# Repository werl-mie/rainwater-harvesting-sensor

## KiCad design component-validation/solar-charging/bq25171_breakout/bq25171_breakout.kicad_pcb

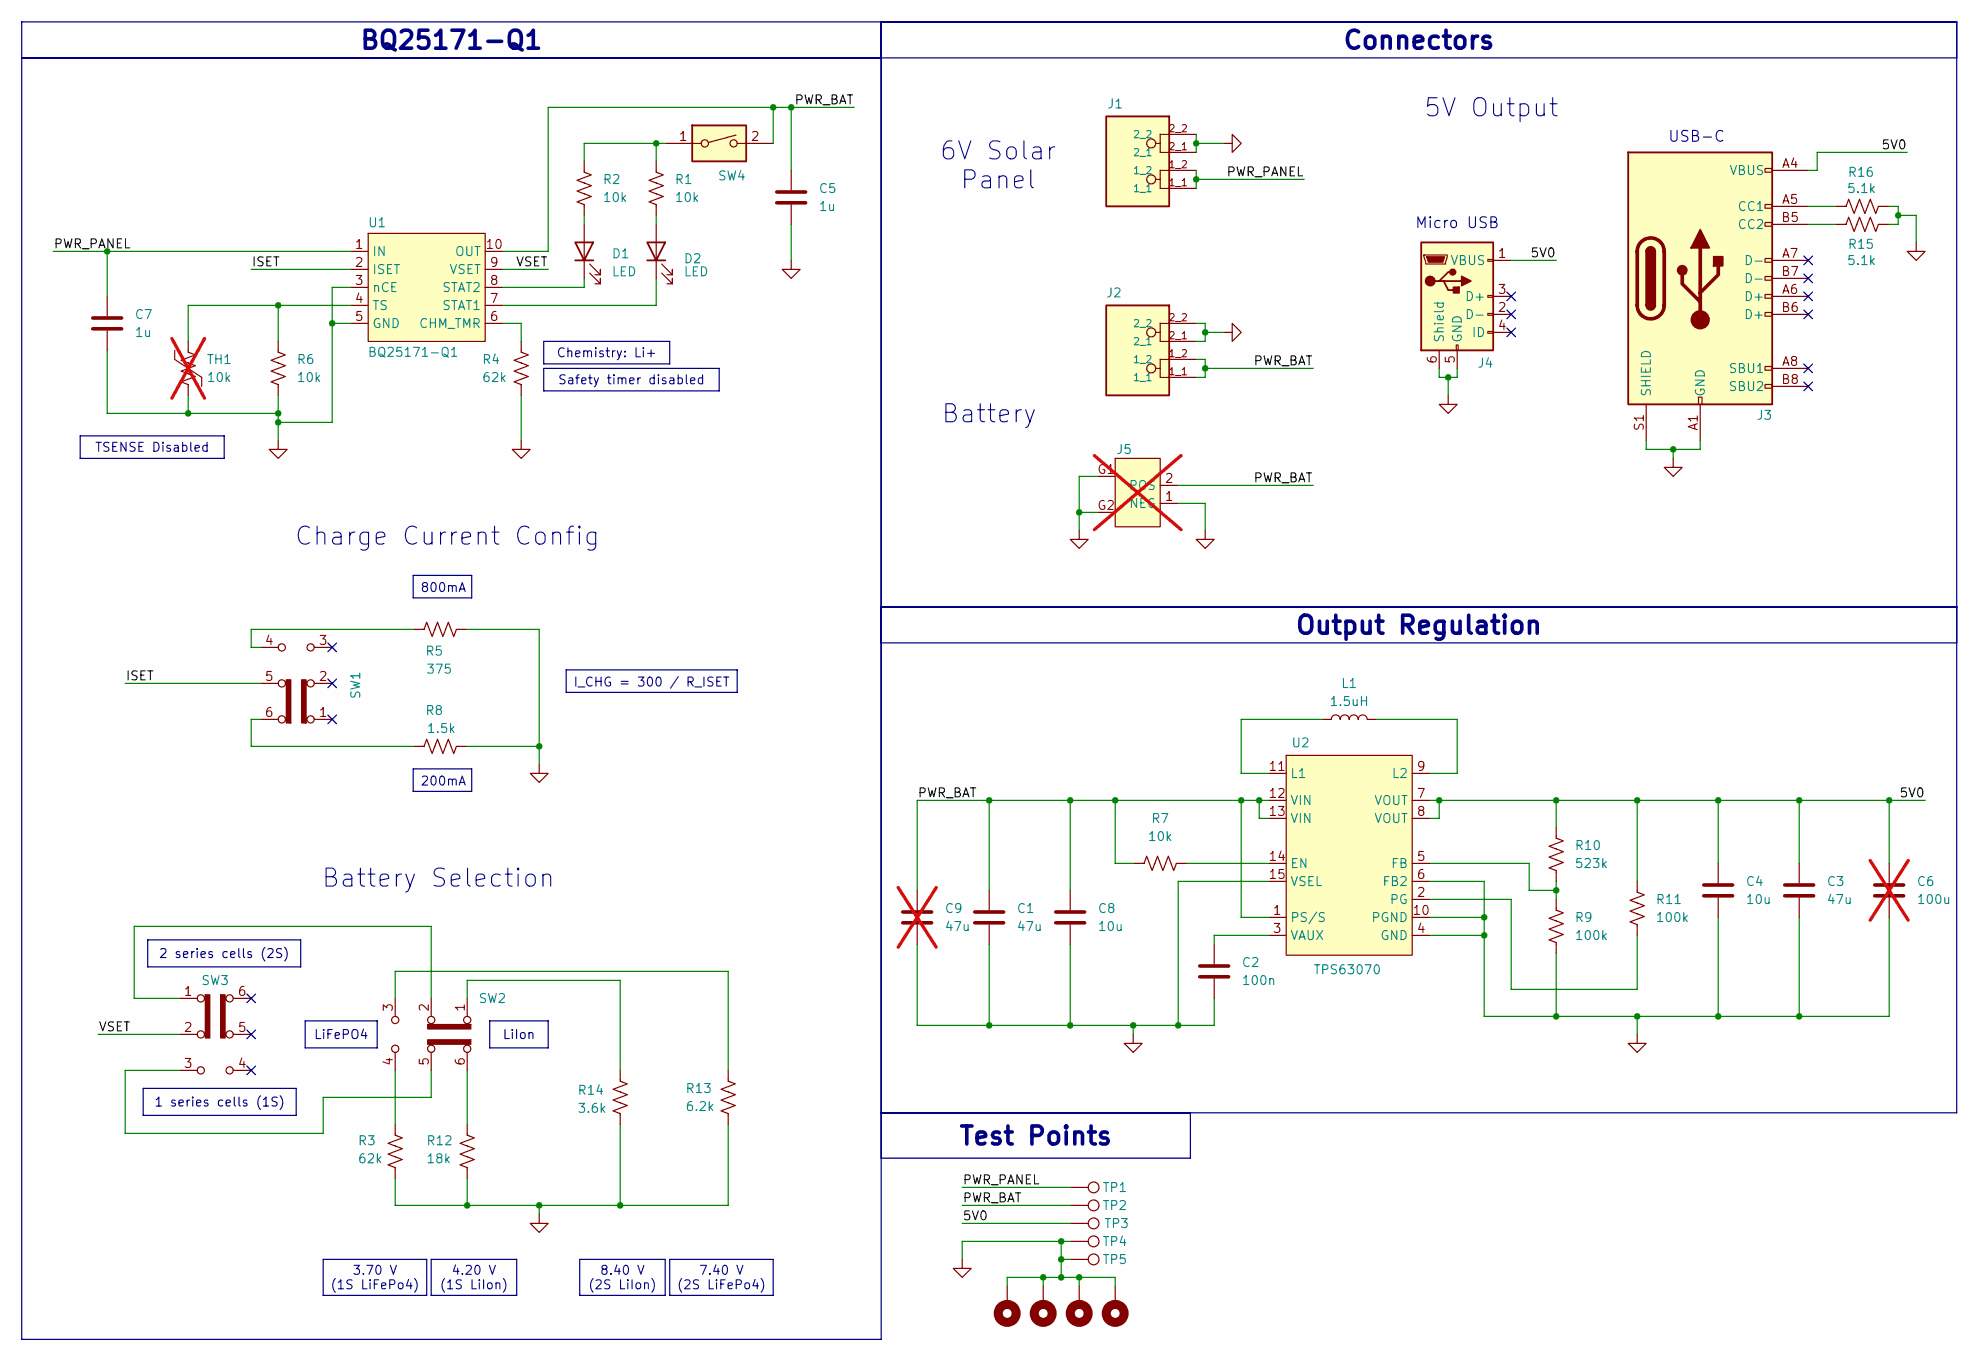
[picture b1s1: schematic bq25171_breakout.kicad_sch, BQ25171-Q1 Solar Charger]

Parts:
C1, C3: 47u; C_1210_3225Metric_Pad1.33x2.70mm_HandSolder
C2: 100n; C_0603_1608Metric_Pad1.08x0.95mm_HandSolder
C4, C8: 10u; C_0603_1608Metric_Pad1.08x0.95mm_HandSolder
C5, C7: 1u; C_0603_1608Metric_Pad1.08x0.95mm_HandSolder
C6: 100u; C_0805_2012Metric_Pad1.18x1.45mm_HandSolder; not fitted
C9: 47u; C_0805_2012Metric_Pad1.18x1.45mm_HandSolder; not fitted
D1, D2: LED; LED_0603_1608Metric
H1, H2, H3, H4: MountingHole_Pad; MountingHole_3.2mm_M3_ISO14580_Pad
J1, J2: 1017503; PHOENIX_1017503; PARTREV 22.12.2017
J3: USB_C_Receptacle_USB2.0_16P; USB_C_Receptacle_XKB_U262-16XN-4BVC11; MPN 12401610E4
J4: USB_B_Micro; USB_Micro-B_Amphenol_10118193-0002LF_Horizontal; MPN 10118193-0002LF
J5: JST_PH_S2B-PH-SM4-TB_1x02-1MP_P2.00mm_Horizontal; not fitted
L1: 1.5uH; L_Changjiang_FXL0420; MPN FXL0420-1R5-M
R1, R2, R6, R7: 10k; R_0603_1608Metric_Pad0.98x0.95mm_HandSolder
R3: 62k; R_0603_1608Metric_Pad0.98x0.95mm_HandSolder; Tolerance 1%
R4: 62k; R_0603_1608Metric_Pad0.98x0.95mm_HandSolder
R5: 375; R_0603_1608Metric_Pad0.98x0.95mm_HandSolder
R8: 1.5k; R_0603_1608Metric_Pad0.98x0.95mm_HandSolder
R9, R11: 100k; R_0603_1608Metric_Pad0.98x0.95mm_HandSolder
R10: 523k; R_0603_1608Metric_Pad0.98x0.95mm_HandSolder
R12: 18k; R_0603_1608Metric_Pad0.98x0.95mm_HandSolder; Tolerance 1%
R13: 6.2k; R_0603_1608Metric_Pad0.98x0.95mm_HandSolder; Tolerance 1%
R14: 3.6k; R_0603_1608Metric_Pad0.98x0.95mm_HandSolder; Tolerance 1%
R15, R16: 5.1k; R_0603_1608Metric_Pad0.98x0.95mm_HandSolder
SW1, SW2, SW3: SW_Slide_DPDT; JLC_SHOU-HAN_MST22D18G2; MPN MST22D18G2
SW4: SW_DIP_x01; JLC_DongGuan_DSIC01LSGET
TH1: 10k; R_Axial_DIN0204_L3.6mm_D1.6mm_P2.54mm_Vertical; MPN 103AT-4; not fitted
TP1, TP2, TP3: TestPoint; TestPoint_Keystone_5000-5004_Miniature
TP4, TP5: TestPoint; TestPoint_Keystone_5019_Miniature
U1: BQ25171-Q1; TI_VSON10_BQ25171; MPN BQ25171-Q1
U2: TPS63070; TI_VQFN15_TPS63070RNMR

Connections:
/5V0: C3.2, C4.2, C6.2, J3.A4 (VBUS), J3.A9 (VBUS), J3.B4 (VBUS), J3.B9 (VBUS), J4.1 (VBUS), R10.1, R11.2, TP3.1, U2.7 (VOUT), U2.8 (VOUT)
/ISET: SW1.5 (B), U1.2 (ISET)
/PWR_BAT: C1.2, C5.2, C8.1, C9.2, J2.1_1, J2.1_2, J5.2 (POS), R7.2, SW4.2, TP2.1, U1.10 (OUT), U2.1 (PS/S), U2.12 (VIN), U2.13 (VIN)
/PWR_PANEL: C7.2, J1.1_1, J1.1_2, TP1.1, U1.1 (IN)
/VSET: SW3.2 (B), U1.9 (VSET)
GND: C1.1, C2.1, C3.1, C4.1, C5.1, C6.1, C7.1, C8.2, C9.1, H1.1, H2.1, H3.1, H4.1, J1.2_1, J1.2_2, J2.2_1, J2.2_2, J3.A1 (GND), J3.A12 (GND), J3.B1 (GND), J3.B12 (GND), J3.S1 (SHIELD), J4.5 (GND), J4.6 (Shield), J5.1 (NEG), J5.G1, J5.G2, R3.1, R4.1, R5.1, R6.1, R8.1, R9.2, R12.1, R13.1, R14.1, R15.2, R16.2, TH1.2, TP4.1, TP5.1, U1.3 (nCE), U1.5 (GND), U1.GND, U2.4 (GND), U2.6 (FB2), U2.10 (PGND), U2.15 (VSEL)
unnamed: D1.2 (A), R2.1
unnamed: D1.1 (K), U1.8 (STAT2)
unnamed: D2.2 (A), R1.1
unnamed: D2.1 (K), U1.7 (STAT1)
unnamed: J3.A5 (CC1), R16.1
unnamed: J3.B5 (CC2), R15.1
unnamed: R1.2, R2.2, SW4.1
unnamed: R3.2, SW2.4 (A)
unnamed: R5.2, SW1.4 (A)
unnamed: R8.2, SW1.6 (C)
unnamed: R12.2, SW2.6 (C)
unnamed: R13.2, SW2.3 (C)
unnamed: R14.2, SW2.1 (A)
unnamed: SW2.2 (B), SW3.1 (A)
unnamed: SW2.5 (B), SW3.3 (C)
unnamed: R4.2, U1.6 (CHM_TMR)
unnamed: R6.2, TH1.1, U1.4 (TS)
unnamed: R7.1, U2.14 (EN)
unnamed: R9.1, R10.2, U2.5 (FB)
unnamed: L1.1, U2.11 (L1)
unnamed: L1.2, U2.9 (L2)
unnamed: R11.1, U2.2 (PG)
unnamed: C2.2, U2.3 (VAUX)

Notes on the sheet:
Micro USB
USB-C
Battery
Charge Current Config
5V Output
Battery Selection
6V Solar Panel
4.20 V (1S LiIon)
LiFePO4
BQ25171-Q1
200mA
7.40 V (2S LiFePo4)
8.40 V (2S LiIon)
TSENSE Disabled
Chemistry: Li+
I_CHG = 300 / R_ISET
1 series cells (1S)
800mA
2 series cells (2S)
Test Points
LiIon
Connectors
3.70 V (1S LiFePo4)
Safety timer disabled
Output Regulation

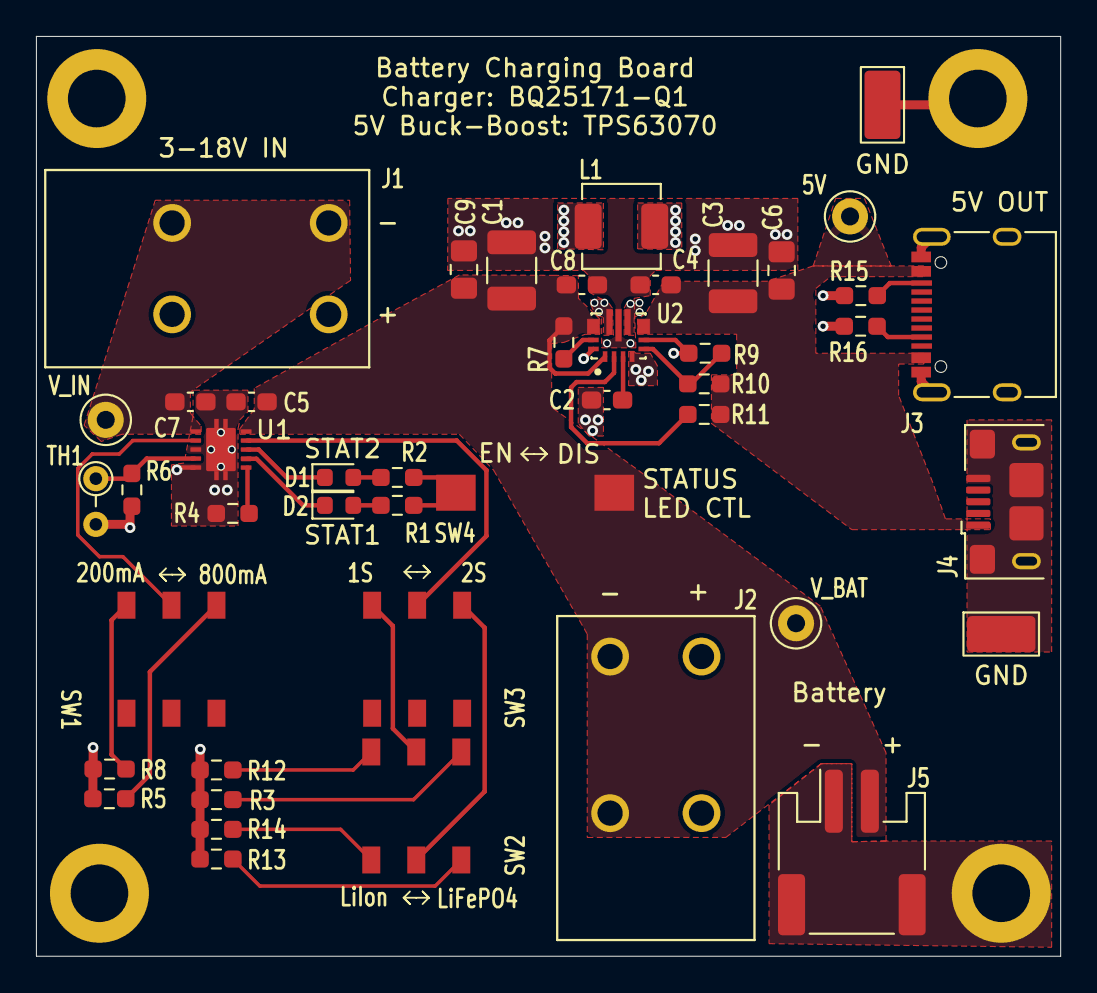
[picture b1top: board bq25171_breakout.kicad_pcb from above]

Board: 2 copper layers, 56.9 x 51.1 mm, 49 parts (0 on the bottom side), 29 nets.

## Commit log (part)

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2023-07-16 Added MWEs for basic FW functionality
2023-07-17 Basic float sensor logging
    Implemented the following functionality:
    - Takes float sensor change as an interrupt (either while sleeping or awake), flagging the change and saving the value into a buffer variable
    - Main loop checks for the flag, which triggers a write to SD card
2023-07-18 Completed code for MWE_InternalRTCBlink
    Used an alarm generated with the internal RTC to blink an LED. Have to set the alarm time to the target time less 1 second, because for some reason when the current time is retrieved with the API, th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
    Verified that the code works when seconds overflows.
2023-07-18 Created MWE_EventTimeoutWithInternalRTC.ino
2023-07-19 Implemented continuous logging timeout
    Notes:
    - Realized I would need to save time of first trigger in order to figure out an interval at the end of the measurement period
    - Due to misunderstanding of the bucket operation, had to change interrupt trigger to FALLING (magnet only activates reed switch in the middle of tipping, NOT at either end)
    - Needed to add a capacitor to debounce the tip bucket reed switch
2023-07-19 Remove attachInterrupts
    Tested this and it turns out they are redundant
2023-07-19 Atomized log_to_sd()
    Made the functionality less specific so that it can used more flexibly (print with/without linebreak, with/without timestamp)
2023-07-20 Added code for 2 extra float sensors
2023-07-21 Removed Serial prints for running off battery
2023-07-24 Fixed debug LED blinking
    debug LEDs that I implemented were not blinking because I have the delay() in code sections without interrupts. Moved the error blinks out of sections where interrupts are disabled...
2023-07-24 Leak test
    Constantly logging periodic data to see if when it stops working. Seems that memory runs out after around 16 seconds (134 logs)
2023-07-24 Removed remaining variable initializations in loops/ISRs
    Also includes:
    - BUILTIN_LED blink as health check
2023-07-24 Removed AHT code
2023-07-24 Added battery voltage monitoring
2023-07-27 Adjusting constants, added log file
2023-07-27 Added watchdog
2023-08-01 Added log files from second test
2023-08-01 Added basic functinoality
    Using D0 and D1 pins. Should test functionality sharing D13 with LED_BUILTIN.
2023-08-18 Code flashed for field trial 1
    - configured pins
    - set bucket timeout to 10
    - added AM2320 code to PCF8523 code
    - added logging of health check
    - removed serial print
2023-10-06 initialized docsify
    includes mermaid test
2023-10-06 removed mermaid test
2023-10-06 Trigger rebuild
2023-10-06 test - removed docsify files
2023-10-06 re-added index.html, removed .nojekyl
2023-10-06 manual index.html test
2023-10-06 Trying building from root
2023-10-06 re-trying build from docs
2023-10-06 Renaming readme.md -> README.md
2023-10-06 removed docs files from root
2023-10-18 initial data cleanup and plotting functionality
    - Reformatting (input -> pre-process2.py -> out.csv)
    - Basic data clean (out.csv -> data_cleanup.py -> out_clean.csv)
    - Basic timescale plotting (plot_time_mpl.py)
2023-10-24 Improved filtering of bucket data and integrated rainfall weather data
2023-10-29 Final fix to extraneous bucket count filtering
2023-11-03 Added cad for V1 sensor
2023-11-24 Added documentation and bucket count conversion
2023-11-24 Attempt to modify example code to work on UNO
2023-11-28 Added bucket-count conversion and resampling
2023-11-30 modified code to work on feather
2023-12-19 Consolidate level data into tank data
    To simplify communication of graphs to Martin
2024-01-08 renamed v1 code folder
2024-01-23 Combined tank level processing with bucket count to rainfall conversion
2024-01-23 Renamed and reorganized folder
2024-01-23 more name changes
2024-01-24 Added script to convert csv to influxDB line format
2024-02-12 Misc progress
    - read-current script for arduino
    - script to parse and publish arduino serial data (influx-publish.py)
    - re-organizing lora code
2024-02-12 Create mwe_grove_tx-rx
    Basic example of tx/rx w/o handshake
2024-02-22 Changes to parsability
    - Added 'tx' and 'rx' headers to serial messages sent from tx/rx nodes to RPi
    - Replaced COTTON_CANDY_ID in read-current.ino with 'cc' header
2024-02-25 Incorrect implementation of check_packets
    function to check for missed vs. received packets. This version won't work as-is because the deque() is being modified as I iterate through it.
2024-02-28 Implemented packet loss checking
    - Basic implementation of linked list to support this
    - Wrote simple test with test data
2024-02-29 Code to run first basic experiment without influx publishing
2024-03-11 lora rx improvements (+ minor power-experiment fix)
    mwe_grove_tx-rx.ino
    - 'fixed' bug where every other tx packet was dropped
    lora-experiment2.py
    - fixed issue where only 1 rx was being read for each 3 tx
    - online missed packet tracking is NOT WORKING
    influx-pubilsh2.py
2024-04-08 Sleeping LoRa module
2024-04-10 v2-cad
2024-04-10 new pot cover assembly
    pot-holder.sldasm
2024-04-11 pot-coupling-v6 changes
    - Made potentiometer slot larger (4.6 -> 4.8 mm)
    - Lowered depth of set screw boss
2024-04-15 pot assembly updates
    pot-coupling-v8
    - Using experimentally validated thread profile diameter (19.8mm)
    pot-holder-3
    - changed angle
2024-04-16 misc changes
    - 5mm slotted hole test
    - enclosure cutout
    - 20mm threaded hole test
2024-04-18 bracket
2024-05-06 Added cellular functionality example code
2024-05-09 Working example of parsing strings from Gateway
2024-05-13 Added main.ino for Arduino MKR NB 1500
    Basic functionality to publish json data
2024-05-13 Update main.ino
    - Added watchdog surrounding only mqqtConnect.
    - Added macro to enable/disable all Serial output
2024-05-14 Cellular - added watchdog
    Keeping the watchdog disabled during cellular (re)connection
2024-05-14 Fixed incorrect parsing of node/parent addresses
2024-05-15 Basic working Tx/Rx
    Tx code: Removed timeout from node_recv()
    Rx code: Removed node_send() (although battery consumption isn't a huge concern anyways)
2024-05-19 wifi changes
    star_rx: adding parsing by message ID
    star_tx: configuring pins
    wifi:
    - adding serial monitor python script for modification
    - Adding wpa_supplicant template
2024-05-20 Basic working serial monitor + tx_rx lora code
2024-05-20 Added tx sd logging
2024-05-20 rx sd card logging
2024-05-20 Flashed Rx/Tx code
    Label "Version 1.0"
2024-07-23 misc reorganizations?
2024-10-26 Parsing of RPi data from sylvias
    Also began data analysis notebook
2025-04-08 misc stuff
2025-04-28 Added solar charging board
2025-06-29 Added sample_grove_rx_and_wire code
2025-07-04 Adriana's LoRa
2025-09-18 Serial output tipping bucket counter
2025-09-18 Create Component_Serial_Tests
2025-09-18 Create rainBucket
2025-10-04 Added nrf_cloud sample
2025-10-11 Remove build files in gitignore
2025-10-12 Created readme and organized files by device
2026-02-20 Create v4_CZ folder
2026-02-20 Create v4_CZ folder attempt 2
2026-02-20 Create RX_ino
2026-02-20 success only sending A0 sensor data
    RADIO_RAW: +TEST: LEN:10, RSSI:-56, SNR:13
    RADIO_RAW: +TEST: RX "386D47280004030601BE"
    ---------------------------
    !!! SUCCESS! Value: 446
    ---------------------------
2026-02-20 Add files via upload
    TX STARTING...
    TX CONFIGURED (915MHz)
    Sending A0: 446
2026-02-20 Add N2.ino for sensor data logging and RTC
    working alone, no battery, no LORA, just printing to serial monitor and SD card
2026-02-20 Add Arduino sketch for sensor data logging
    working alone, no battery, no LORA, printing to SD card and serial monitor
2026-02-20 ADDING SENSOR PRINTOUTS
    LOCAL,Turbidity,1771604971,302
    LOCAL,Lux,1771604971,5
    LORA,REMOTE_LEAF,1771604974,1
    LORA,REMOTE_FLOAT_BOT,1771604981,1
    LOCAL,Pressure,1771604986,117
    LOCAL,Turbidity,1771604986,302
2026-02-20 SENDING DATA TO RX
    CAN'T GET THE PRINTING TO WORK ON THIS SERIAL MONITOR, BUT ALL STATUS ON THE RX SERIAL MONITOR
2026-02-20 Implement 10-minute bucket reset logic
    Added logic to reset bucket count after 10 minutes of inactivity and updated last active timestamp tracking.
2026-02-20 REPARSE SENSOR VALUES STILL WORKING ON TURBIDITY, LUX, PRESSURE
2026-02-20 turbid, lux, pressure needs work
    Refactor pressure and turbidity sensor readings. Adjust calculations for pressure and log data format for Lux.
2026-03-18 lux and pressure good. waiting on resistors for turbid.
    Updated the analog pressure pin and modified the readTimerSensors function to log raw pressure values and improved lux sensor handling.
2026-03-19 Create turbid_testing
2026-03-19 working
2026-03-19 all working on RX. Can't get info from TX
2026-03-19 Add transmitter test script for LoRa module
    Implement a test script for LoRa transmitter functionality with setup and loop for sending packets.
2026-03-19 Add receiver test for GroveLora module
2026-03-19 Refactor LORA_RX.ino for clarity and efficiency
2026-03-19 Refactor LORA_TX.ino with debugging and new features
    Refactor LORA_TX.ino to improve structure and add debugging features.
2026-03-19 final working rx
2026-03-19 final working tx
2026-03-20 ready
2026-04-07 Create indiv_component_testing
2026-04-07 Add RTC hardware test code to RTC.ino
2026-04-07 Refactor RTC setup and synchronization process
2026-04-24 Add digital read script for Adafruit RP2040
    This script reads a digital input from pin 9 on the Adafruit RP2040 and outputs the result to the Serial Monitor.
2026-05-07 Add initial implementation of sensor data logging
2026-05-08 Refactor pin definitions and clean up code
    Updated pin definitions and commented out unused code for clarity.
